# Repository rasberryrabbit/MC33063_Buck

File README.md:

# MC33063_Buck
Simple MC33063 Buck Converter

12v to 5v buck converter.

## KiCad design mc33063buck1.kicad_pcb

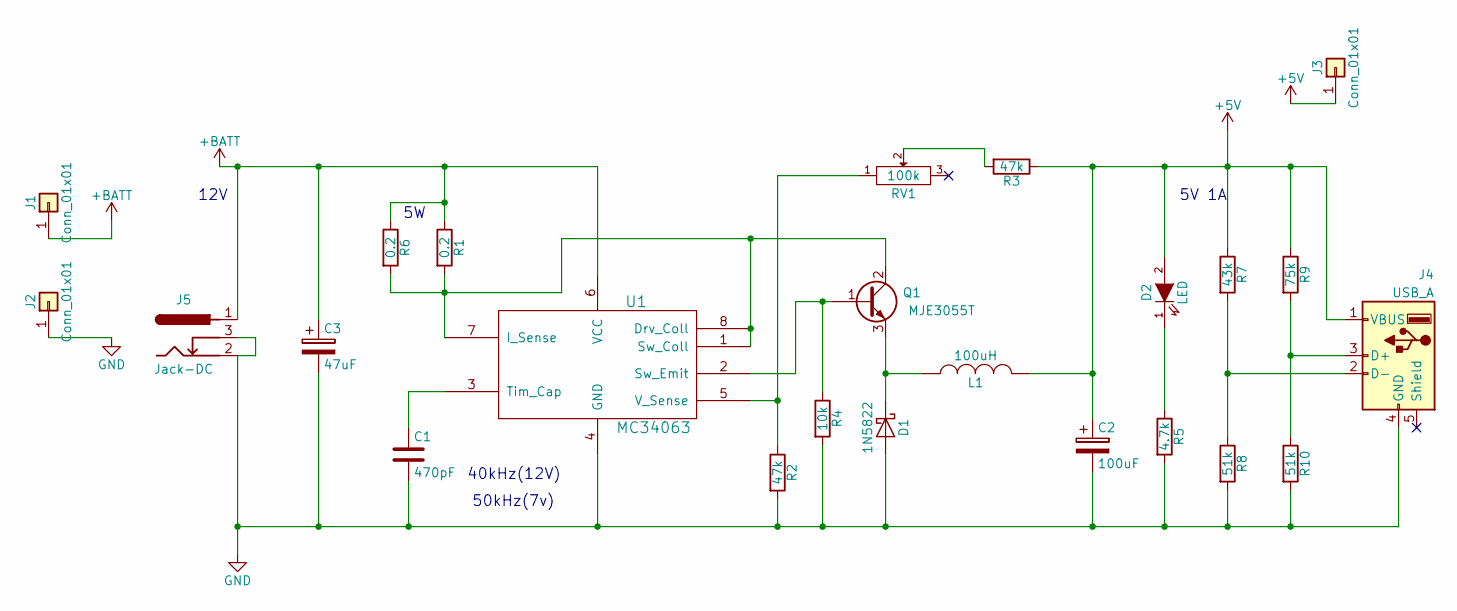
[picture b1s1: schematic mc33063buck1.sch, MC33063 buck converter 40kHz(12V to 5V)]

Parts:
C1: 470pF; C_Disc_D11.0mm_W5.0mm_P5.00mm
C2: 100uF; CP_Radial_D12.5mm_P5.00mm
C3: 47uF; CP_Radial_D12.5mm_P5.00mm
D1: 1N5822; D_DO-201AD_P15.24mm_Horizontal
D2: LED; LED_D5.0mm
J1, J2, J3: Conn_01x01; Pin_d1.3mm_L11.0mm
J4: USB_A
J5: Jack-DC; BARREL_JACK
L1: 100uH; L_Toroid_Vertical_L24.6mm_W15.5mm_P11.44mm_Pulse_KM-4
Q1: MJE3055T; TO-220_Neutral123_Vertical
R1, R6: 0.2; R_Bare_Metal_Element_L21.3mm_W4.8mm_P20.30mm
R2, R3: 47k; R_Axial_DIN0309_L9.0mm_D3.2mm_P2.54mm_Vertical
R4: 10k; R_Axial_DIN0309_L9.0mm_D3.2mm_P2.54mm_Vertical
R5: 4.7k; R_Axial_DIN0309_L9.0mm_D3.2mm_P2.54mm_Vertical
R7: 43k; R_Axial_DIN0309_L9.0mm_D3.2mm_P2.54mm_Vertical
R8, R10: 51k; R_Axial_DIN0309_L9.0mm_D3.2mm_P2.54mm_Vertical
R9: 75k; R_Axial_DIN0309_L9.0mm_D3.2mm_P2.54mm_Vertical
RV1: 100k; Potentiometer_Trimmer_ACP_CA6v_Horizontal
U1: MC34063; DIP-8_W7.62mm_LongPads

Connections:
+5V: C2.1, D2.2 (A), J3.1, J4.1 (VBUS), L1.2, R3.1, R7.1, R9.1
+BATT: C3.1, J1.1, J5.1, R1.1, R6.1, U1.6 (VCC)
GND: C1.2, C2.2, C3.2, D1.2 (A), J2.1, J4.4 (GND), J5.2, J5.3, R2.2, R4.2, R5.2, R8.2, R10.2, U1.4 (GND); also elsewhere on the board
unnamed: C1.1, U1.3 (Tim_Cap)
unnamed 4: D1.1 (K), L1.1, Q1.3 (E); also elsewhere on the board
unnamed: D2.1 (K), R5.1
unnamed: J4.2 (D-), R7.2, R8.1
unnamed: J4.3 (D+), R9.2, R10.1
unnamed: Q1.1 (B), R4.1, U1.2 (Sw_Emit)
unnamed: Q1.2 (C), R1.2, R6.2, U1.1 (Sw_Coll), U1.7 (I_Sense), U1.8 (Drv_Coll)
unnamed: R2.1, RV1.1, U1.5 (V_Sense)
unnamed: R3.2, RV1.2

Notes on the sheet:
5V 1A
40kHz(12V)
12V
50kHz(7v)

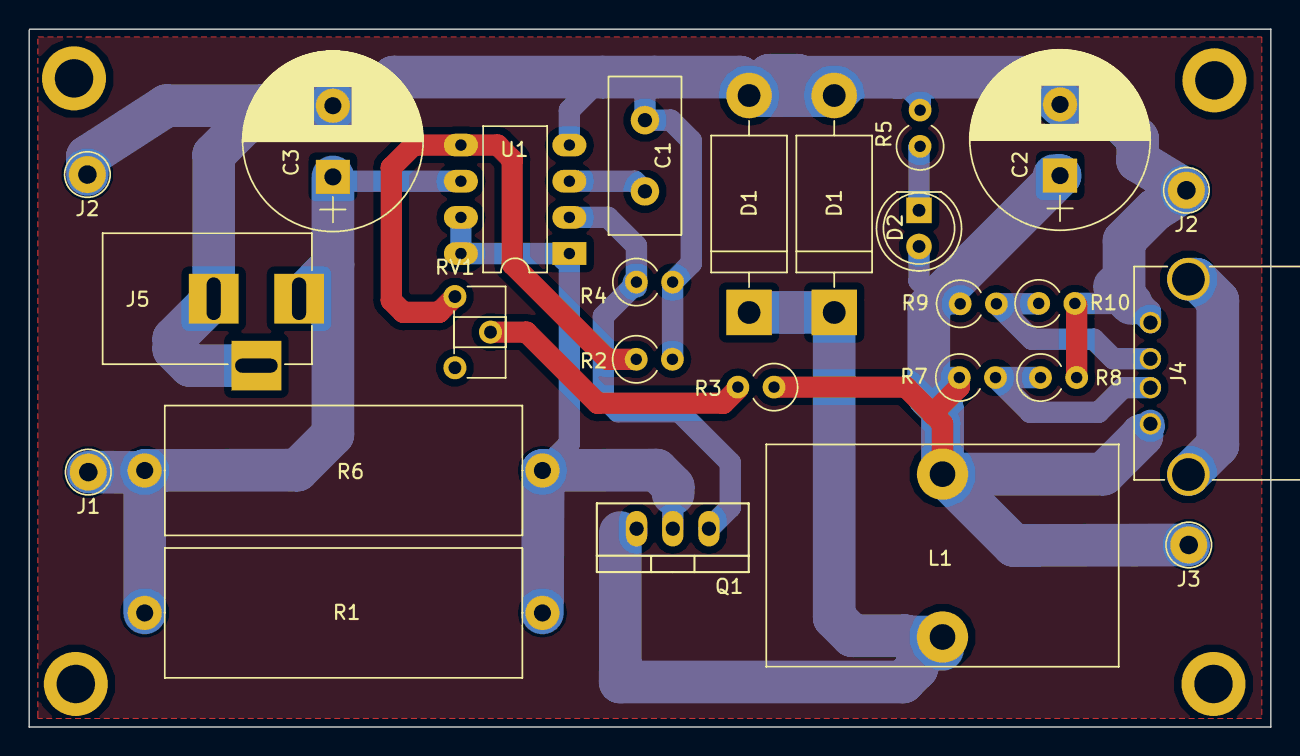
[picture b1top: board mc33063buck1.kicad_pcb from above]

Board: 2 copper layers, 87.2 x 49.0 mm, 26 parts (0 on the bottom side), 12 nets.

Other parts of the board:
D1#2: 1N5822; D_DO-201AD_P15.24mm_Horizontal
J2#2: Conn_01x01; Pin_d1.3mm_L11.0mm

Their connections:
GND: D1#2.2, J2#2.1; also elsewhere on the board
unnamed 4: D1#2.1; also elsewhere on the board

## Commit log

2015-08-22 first commit.
2018-07-16 make pcb layout.
2018-07-26 fix resistor size and lines.
2018-08-07 update.
2018-08-07 add files.
2019-03-06 Add 3v to 9v boost.
